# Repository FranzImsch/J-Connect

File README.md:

# J-Link Adapter Boards

20P JTAG to TAG-Connect TC2030 and  
20P JTAG to 10P JTAG (1.27mm) adapter boards.

### Features:
* 5V to 3.3V LDO and power good LED,
* button to reset the target device,
* VCOM breakout.

### PCB
The ideal PCB thickness would be 2.0mm, but 1.6mm is much cheaper and works as well.

## Tag-Connect Adapter

## 10P Adapter
A jumper can be added to connect RX and TX to the pins 7 and 8 respectively. (TX and RX are not in the standard 10P pinout!)

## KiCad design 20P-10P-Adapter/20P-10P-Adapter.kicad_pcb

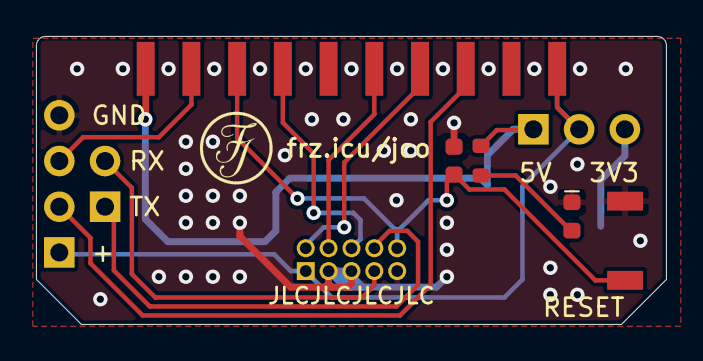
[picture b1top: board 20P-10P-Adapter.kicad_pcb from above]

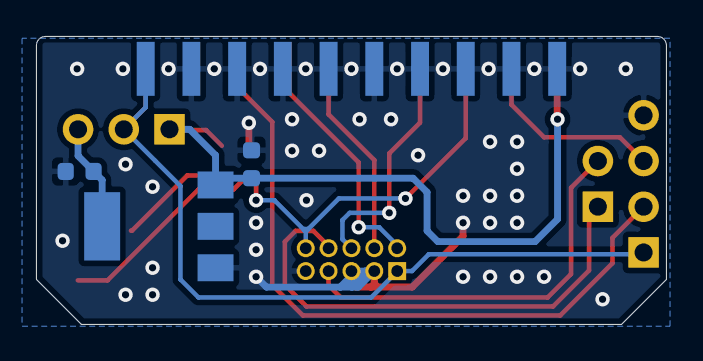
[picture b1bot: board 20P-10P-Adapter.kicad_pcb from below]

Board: 2 copper layers, 35.0 x 16.0 mm, 12 parts (3 on the bottom side), 13 nets.

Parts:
C1: 1µF; C_0603_1608Metric
C2: 4.7µF; C_0603_1608Metric
C3: C_Small; C_0603_1608Metric
D1: Power LED; LED_0603_1608Metric
J1: Conn_02x10_Odd_Even; Jlink-Conn-20P-PCB
J2: 10P SWD; IDC-Header_2x05_P1.27mm_Latch_Vertical
J3: Conn_01x04; PinHeader_1x04_P2.54mm_Vertical
J4: Conn_01x02; PinHeader_1x02_P2.54mm_Vertical
JP1: Jumper_NC_Dual; PinHeader_1x03_P2.54mm_Vertical
R1: 1.5kΩ; R_0603_1608Metric
SW1: SW_Push; SW_DIP_SPSTx01_Push_TSA343G00-250J2
U1: LDL1117S33R; SOT-223-3_TabPin2

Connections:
+3V3: C2.1, JP1.3, U1.2
+5V: C1.2, J1.19, JP1.1, R1.1, U1.3
GND: C1.1, C2.2, C3.1, D1.1, J1.4, J1.6, J1.8, J1.10, J1.12, J1.14, J1.16, J1.18, J1.20, J2.3, J2.5, J2.9, J3.4, SW1.2, U1.1
unnamed: D1.2, R1.2
RESET: C3.2, J1.15, J2.10, SW1.1
SWCLK: J1.9, J2.4
SWDIO: J1.7, J2.2
SWO: J1.13, J2.6
SWO-RX: J2.7, J4.2
SWO-TX: J2.8, J4.1
VCOM_RX: J1.17, J3.3
VCOM_TX: J1.5, J3.2
VTref: J1.1, J1.2, J2.1, J3.1, JP1.2

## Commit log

2021-07-31 initialising repo
2021-07-31 .DS_Store banished...
2021-07-31 added description to renderings
2021-08-19 added 10P. adapter board
